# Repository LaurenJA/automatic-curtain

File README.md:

# Automatic Curtain Opener

The automatic curtain opener allows curtain to be opened and closed: 
* Remotely 
* At specific times 
* Automatically at dawn and dusk 

Thus allowing users to:
* Wake up naturally using the light of the sun 
* Appear at home, when away travelling

This real-time project utilises a Raspberry Pi 3, light and proximity sensors, a motorised pulley system, custom PCB boards, and a web GUI. 

More details about the hardware and software can be found in the [Wiki](https://github.com/LaurenJA/automatic-curtain/wiki.

### System Overview 

Below is an simple overview of how the deployed sensors and motor could be positioned on the curtain pole. 

### Build Instructions 

The code related to this project can be found in the code folder.

#### Requirements 
CMake version 3.10 

Python version 3.6

Django version 2.11.1

#### Build 
Compile the project 
``` 
make
```

To run the program
``` 
sudo ./server 
```

To open the folder of the web app(which is named as mysite in this project).
```
cd ...
```

Then run the server.
```
python3 manage.py runserver
```

### Project Evaluation

#### Sampling rate
Under the Auto model, the status will be checked every 0.2 seconds, so the sampling rate should be 5 times per seconds.
#### Bus Protocol
The interface of the light sensor:OPT3001 and proximity sensor:APDS9960 are I2C, so use the I2C bus protocol.
#### Low level implementation: kernel or user space and why?
User space. As this can provided fast enough sampling and processing, without having to modeify the kernel. 
#### Data flow from hardware to GUI to output with data formats, latencies,processing and conversions.
Not provided
#### Buffering of data: how many samples?
The buffering of data is 8k, which is enough for this project.
#### How does the buffering impact on the realtime performance and how much latency is introduced?
For the large amount of data, the buffering of data should be higher, however,for our project, the ultra-small amout of date has no influence on realtime performance.
#### How many threads are needed and/or how can the load be distributed to allow a responsive application?
There are two threads, one is for communication with GUI, and one if to achieve function of the command.
#### Structure of the software in classes, associated unit tests to turn it into reliable software
The required software is provided within the code folder. This can be compiled and executed on the Raspberry pi by using the following command: make ./server within the code directory. And the test code also can be found in the test folder.
Overview of the software can be found in the wiki
#### Team structure: which roles in a team of 3 and how equal contributions are guaranteed?
The team members and roles are as follow:
Lauren Astell: Hardware (including PCB Design)
Jing Wang: Code of light sensor,proximity sensor,motor controller and main function implementaion and test.
Jianan Kan:GUI Implementation
#### How much time is allocated to hard, software and debugging and how is this interleaved?
Every memeber will do their specific work, and control the process by themselves. The final work achieved by Lauren.
#### Which version control software is used? How are releases / milestones done and numbered?
GIT was used. Versions are number vX.Y, where X is a major change and Y is a minor. 
The project is currently at realease v1.0
#### What is the release strategy / publication / publicity? How is that measured and deemed to be successful?
To release the project, a release was created on the GitHub so any user that wishes to create this project themselves can download it. 
####  Measurement of success of the application in the context of the problem given and evaluation of it.

#### How to implement the GUI? Permitted refresh rate and latency resulted from it.
To use the web page as the GUI, the web page is coded in django. Everyone who get the website can control the curtain in the same network. The instruction can be sent by GUI.

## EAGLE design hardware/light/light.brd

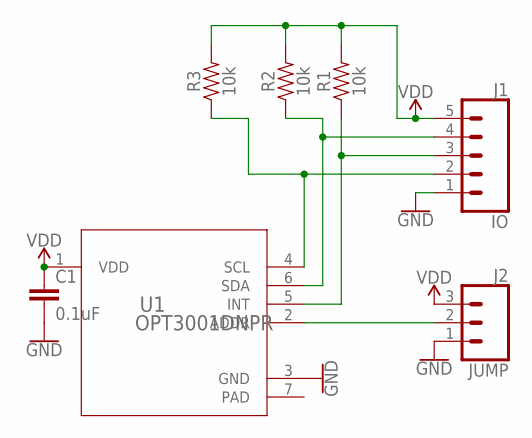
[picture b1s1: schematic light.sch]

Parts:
C1: 0.1uF; CAP-PTH-SMALL-KIT
J1: IO; 1X05
J2: JUMP; 1X03
R1, R2, R3: 10k; AXIAL-0.3
U1: OPT3001DNPR; DNP0006A

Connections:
ADD: J2.2, U1.2 (ADDR)
GND: C1.2, J1.1, J2.1, U1.3 (GND)
INT: J1.3, R1.P$1 (1), U1.5 (INT)
SCL: J1.2, R3.P$1 (1), U1.4 (SCL)
SDA: J1.4, R2.P$1 (1), U1.6 (SDA)
VDD: C1.1, J1.5, J2.3, R1.P$2 (2), R2.P$2 (2), R3.P$2 (2), U1.1 (VDD)

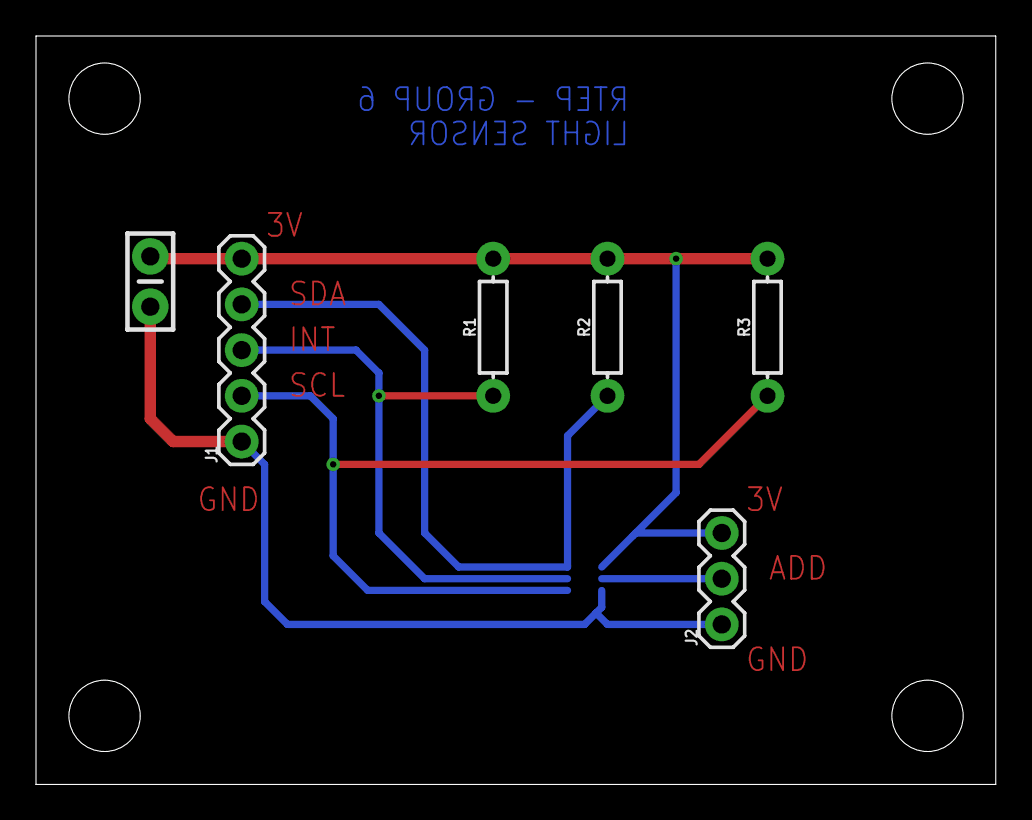
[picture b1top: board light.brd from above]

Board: 2 copper layers, 53.3 x 41.6 mm, 7 parts (1 on the bottom side), 6 nets.

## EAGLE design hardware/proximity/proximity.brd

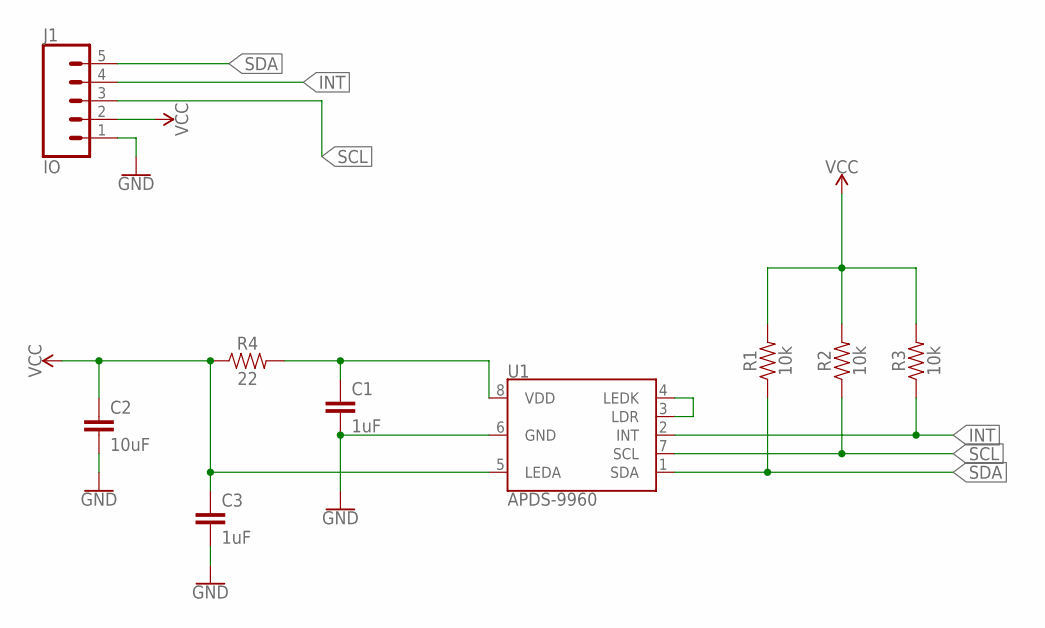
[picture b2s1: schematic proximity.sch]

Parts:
C1, C3: 1uF; CAP-PTH-SMALL-KIT
C2: 10uF; CAP-PTH-SMALL-KIT
J1: IO; 1X05
R1, R2, R3: 10k; AXIAL-0.3
R4: 22; AXIAL-0.3
U1: APDS-9960

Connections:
GND: C1.2, C2.2, C3.2, J1.1, U1.6 (GND)
INT: J1.4, R3.P$1 (1), U1.2 (INT)
unnamed: U1.3 (LDR), U1.4 (LEDK)
unnamed: C1.1, R4.P$2 (2), U1.8 (VDD)
SCL: J1.3, R2.P$1 (1), U1.7 (SCL)
SDA: J1.5, R1.P$1 (1), U1.1 (SDA)
VCC: C2.1, C3.1, J1.2, R1.P$2 (2), R2.P$2 (2), R3.P$2 (2), R4.P$1 (1), U1.5 (LEDA)

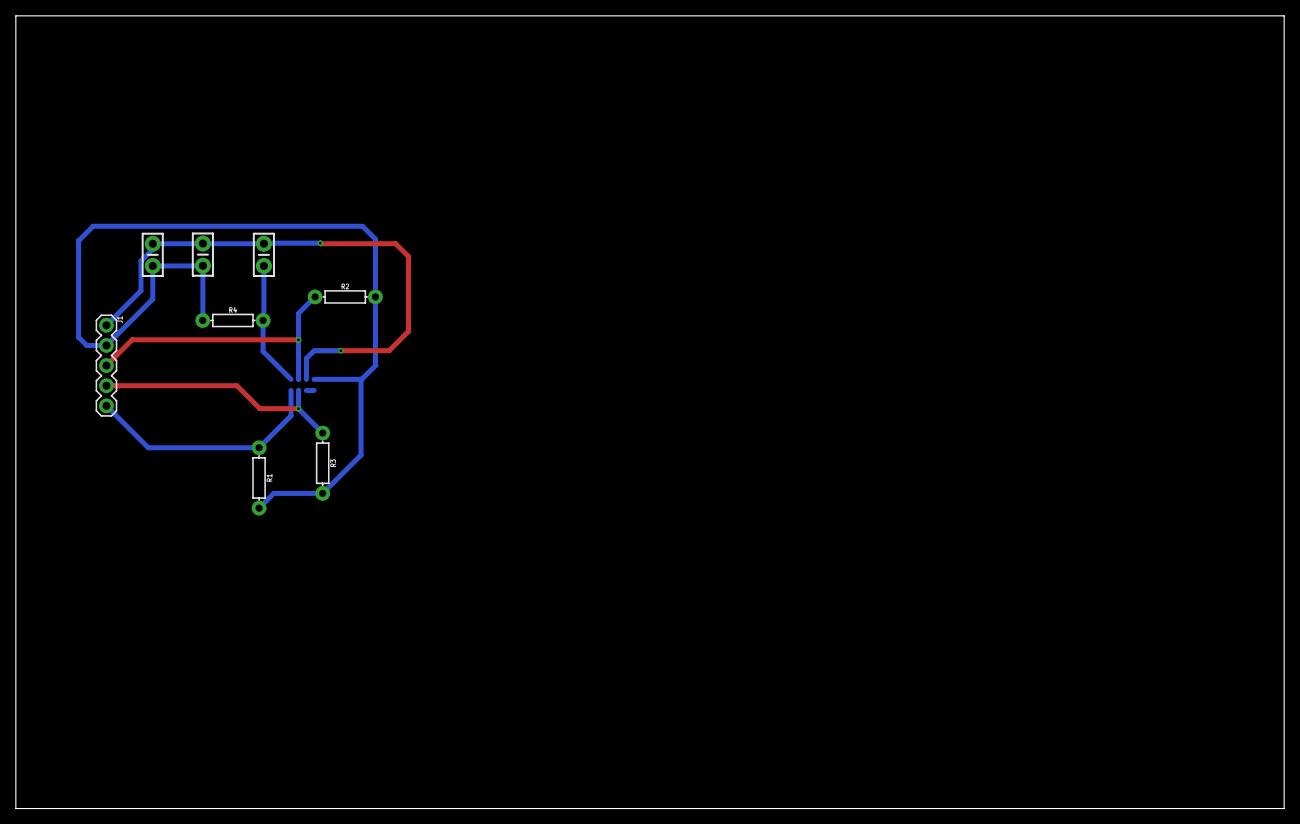
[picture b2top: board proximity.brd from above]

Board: 2 copper layers, 160.0 x 100.0 mm, 9 parts (1 on the bottom side), 7 nets.

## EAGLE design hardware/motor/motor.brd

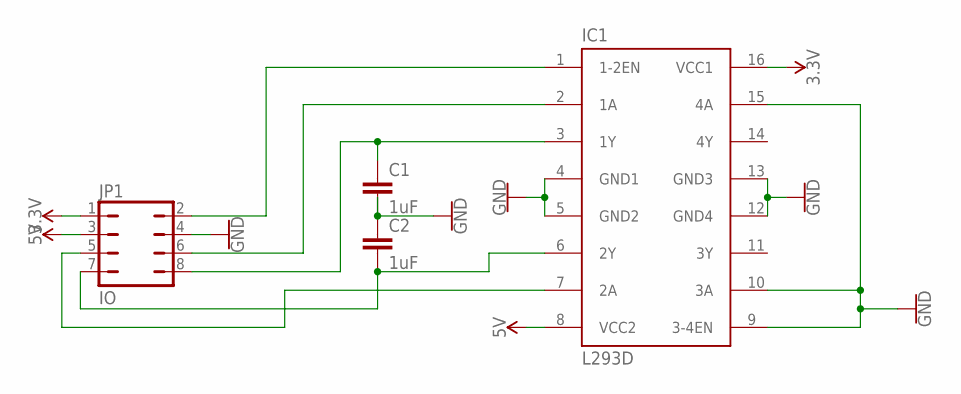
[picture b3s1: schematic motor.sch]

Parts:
C1, C2: 1uF; CAP-PTH-SMALL-KIT
IC1: L293D; DIL16
JP1: IO; JP4Q

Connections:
3.3V: IC1.16 (VCC1), JP1.1
5V: IC1.8 (VCC2), JP1.3
GND: C1.2, C2.1, IC1.4 (GND1), IC1.5 (GND2), IC1.9 (3-4EN), IC1.10 (3A), IC1.12 (GND4), IC1.13 (GND3), IC1.15 (4A), JP1.4
unnamed: C1.1, IC1.3 (1Y), JP1.8
unnamed: C2.2, IC1.6 (2Y), JP1.7
unnamed: IC1.1 (1-2EN), JP1.2
unnamed: IC1.2 (1A), JP1.6
unnamed: IC1.7 (2A), JP1.5

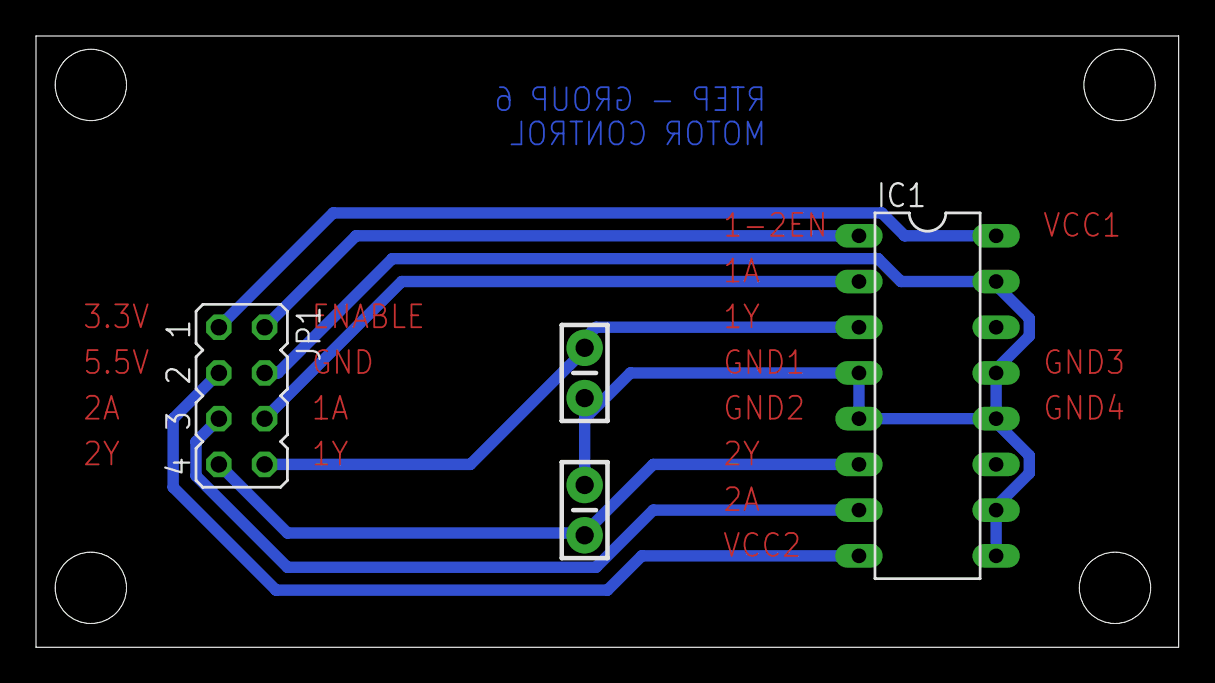
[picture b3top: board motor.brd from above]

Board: 2 copper layers, 63.5 x 34.0 mm, 4 parts (0 on the bottom side), 8 nets.

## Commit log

2018-01-17 Add MIT License file
2018-02-14 Add system overview diagram
2018-02-14 Update README.md
    Add system overview picture and description
2018-03-12 Schematic and PCB files for motor board layout
2018-03-12 proximity sensor schematic and pcb layout
2018-03-13 Create RPI
2018-03-13 Create UDP
2018-03-21 Create class structure for motor control
2018-03-21 Added build instructions
2018-03-21 Add link to Wiki page
2018-04-11 change
2018-04-13 code
2018-04-13 Create APDS9960-PROXIMITY SENSOR
2018-04-13 Update Makefile
2018-04-13 proximity sensor
2018-04-13 light sensor
2018-04-14 interface
2018-04-15 Create test
2018-04-16 Schematic and layout for light sensor

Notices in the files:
parts and their libraries:
SparkFun-Connectors: Licensing: Creative Commons ShareAlike 4.0 International - https://creativecommons.org/licenses/by-sa/4.0
